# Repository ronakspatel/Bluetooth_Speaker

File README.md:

# Bluetooth Speaker Project  

Hello! My name is **Ronak Patel**, and this repository contains my work on building a **Bluetooth speaker with a metadata display**.  

At a high level, the flow from **phone → speaker** involves:  
1. Reception of the Bluetooth audio signal  
2. Conversion to analog audio  
3. Amplification and playback  

While commercial modules worked out of the box, I wanted to explore improvements and unique features:  
- A **portable speaker** with a **metadata display** (song title, artist, album)  
- An **audio visualizer** running on a TFT screen  
- My **first custom amplifier PCB**, designed in *KiCad*, to replace a noisy off-the-shelf board  

This project became an opportunity to learn the **full EE process**: embedded programming (ESP32), PCB design, and iterative prototyping.  

---

## High-Level Design  

### ESP32-WROOM-32 (Bluetooth Classic, A2DP sink)  
- Uses the [pschatzmann A2DP library](https://github.com/pschatzmann/ESP32-A2DP)  
- Supports **Bluetooth Classic**, which is required for A2DP audio  
- Provides metadata callback for song information  

### PCM5102A DAC  
- Converts I²S stream from ESP32 into high-quality analog audio  
- Chosen instead of ESP32’s internal 8-bit DAC (too low quality)  

### 1.8" TFT Display (128×160 px)  
- Upper half: **metadata** (title, artist, album)  
- Lower half: **audio visualizer** via FFT bins  
- Smooth GUI achieved by pushing the display as a **sprite**  

### Power System  
- **3S2P Li-ion battery pack** + **buck converter**  
- Amplifier powered directly from the battery via DC barrel jack  
- ESP32 power tapped via screw terminal  

---

## Amplifier Board (Custom PCB)  

### TPA3116D2 (Class D Audio Amp)  
- High power output, good fidelity  
- Efficient for **battery-powered** audio  

### TPS611781 (Boost Converter)  
- Steps up battery to ~19.6V  
- Stable voltage maximizes amplifier power output  

### NE5532 Op-Amp + RK09712200MY Potentiometer  
- Provides **stereo volume control**  
- Low output impedance prevents input impedance mismatch  

---

## Current Status  

- Speaker is **functional**, with enclosure designed (cutting pending)  
- Issues with the **RK09712200MY pot** (rated for 9V, running at 20V):  
  - Behaves like a balance control instead of volume  
  - Both output channels not stable under all loads  
- Audio visualizer: bass frequencies **dominate FFT output**, needs better equalization  

---

## Future Improvements  
- Integrate **all components** into one PCB  
- Refine **FFT visualization** for better frequency distribution  
- Replace problematic **potentiometer** with a properly rated alternative  
- Improve **enclosure fabrication** for a polished final product  

---

## Pictures

---

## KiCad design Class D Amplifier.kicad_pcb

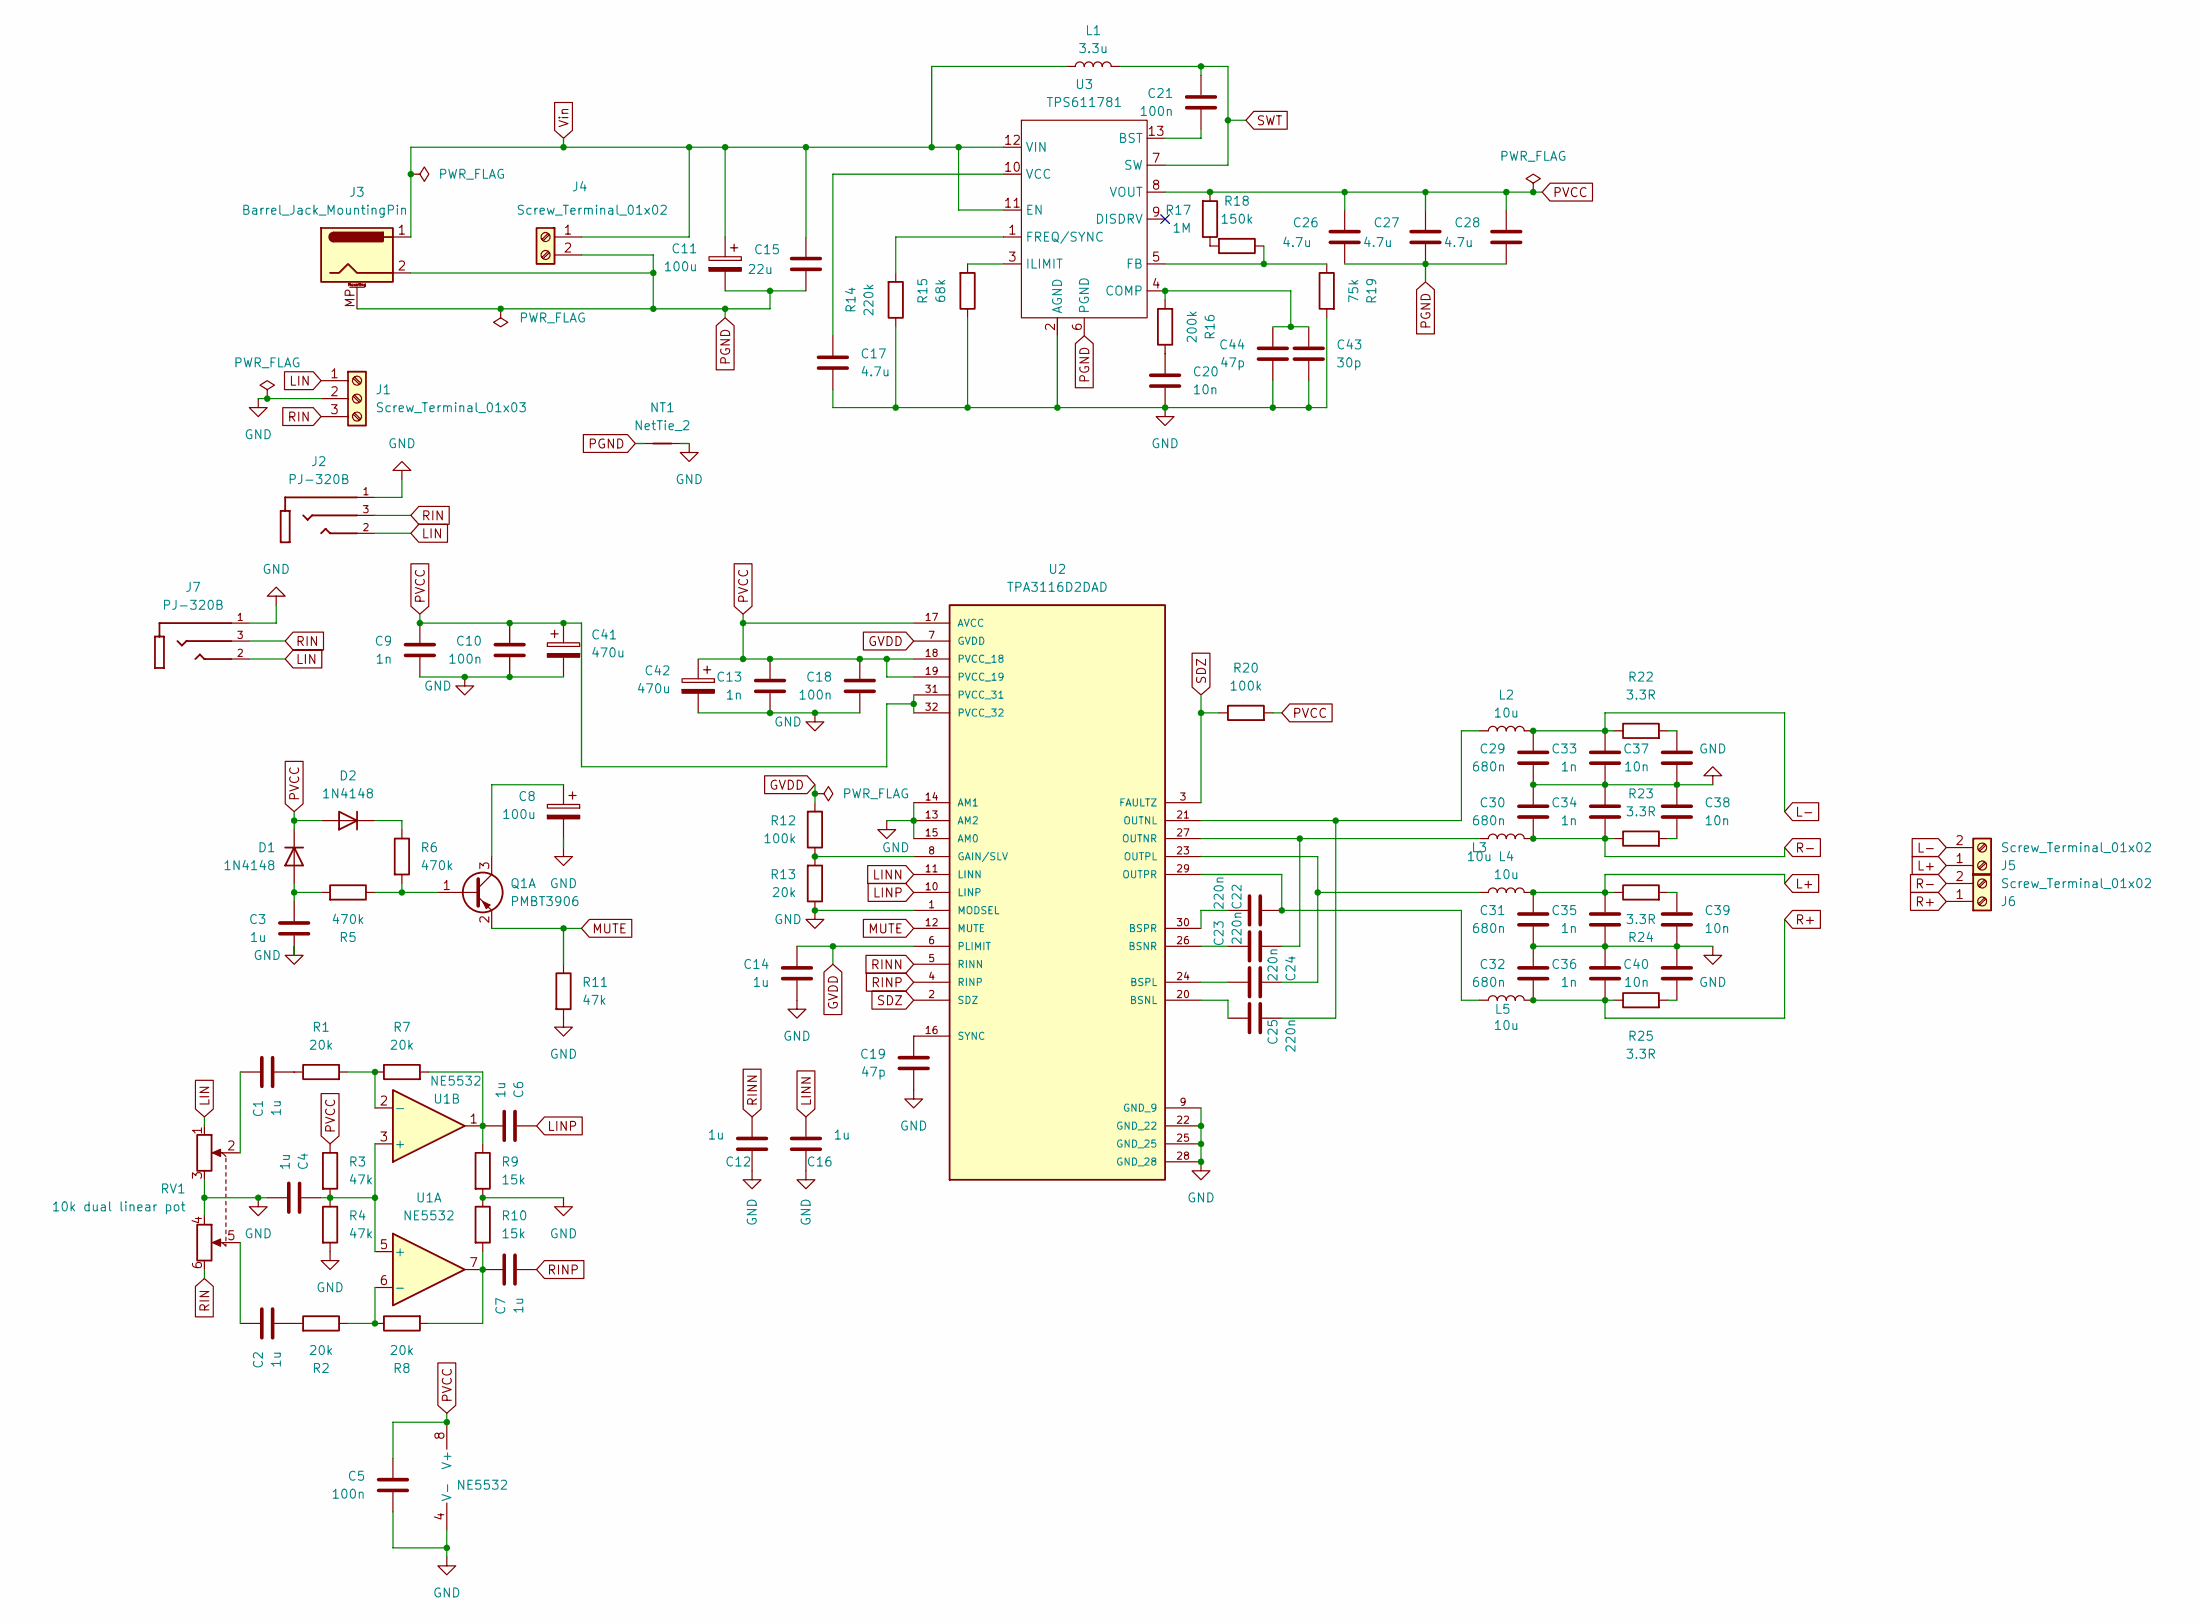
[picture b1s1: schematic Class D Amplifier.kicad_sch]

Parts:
C1, C2, C3, C4, C6, C7, C12, C14, C16: 1u; C_0805_2012Metric
C5, C10, C18: 100n; C_0805_2012Metric
C8, C11: 100u; CP_Radial_D6.3mm_P2.50mm
C9, C13, C33, C34, C35, C36: 1n; C_0805_2012Metric
C15: 22u; C_0805_2012Metric
C17, C26, C27, C28: 4.7u; C_0805_2012Metric
C19: 47p; C_0805_2012Metric
C20: 10n; C_0603_1608Metric
C21: 100n; C_0603_1608Metric
C22, C23, C24, C25: 220n; C_0805_2012Metric
C29, C30, C31, C32: 680n; C_Rect_L7.0mm_W3.5mm_P5.00mm
C37, C38, C39, C40: 10n; C_0805_2012Metric
C41, C42: 470u; CP_Radial_D10.0mm_P5.00mm
C43: 30p; C_0603_1608Metric
C44: 47p; C_0603_1608Metric
D1, D2: 1N4148; D_SOD-123
J1: Screw_Terminal_01x03; TerminalBlock_bornier-3_P5.08mm
J2, J7: PJ-320B; AUDIO_TH_PJ-3210-4A
J3: Barrel_Jack_MountingPin; BarrelJack_CUI_PJ-063AH_Horizontal
J4, J5, J6: Screw_Terminal_01x02; TerminalBlock_bornier-2_P5.08mm
L1: 3.3u; L_Sunlord_MWSA1003S
L2, L3, L4, L5: 10u; L_KOHERelec_MDA7030
NT1: NetTie_2; NetTie-2_SMD_Pad0.5mm
Q1: PMBT3906; SOT-23-3
R1, R2, R7, R8, R13: 20k; R_0805_2012Metric
R3, R4, R11: 47k; R_0805_2012Metric
R5, R6: 470k; R_0805_2012Metric
R9, R10: 15k; R_0805_2012Metric
R12, R20: 100k; R_0805_2012Metric
R14: 220k; R_0603_1608Metric
R15: 68k; R_0603_1608Metric
R16: 200k; R_0603_1608Metric
R17: 1M; R_0603_1608Metric
R18: 150k; R_0603_1608Metric
R19: 75k; R_0603_1608Metric
R22, R23, R24, R25: 3.3R; R_0805_2012Metric
RV1: 10k dual linear pot; Potentiometer_Alps_RK097_Dual_Horizontal
U1: NE5532; SOIC-8_3.9x4.9mm_P1.27mm
U2: TPA3116D2DAD; SOP65P810X115-32N; PARTREV G
U3: TPS611781; RNW0013A

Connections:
GVDD: C14.1, R12.2, U2.6 (PLIMIT), U2.7 (GVDD)
L+: C31.1, C35.1, J5.1, L4.1, R24.1
L-: C29.1, C33.1, J5.2, L2.2, R22.1
LIN: J1.1, J2.2, J7.2, RV1.1
LINN: C16.2, U2.11 (LINN)
MUTE: Q1.2 (E1), R11.1, U2.12 (MUTE)
unnamed: C1.1, RV1.2
unnamed: C1.2, R1.1
unnamed: C2.1, RV1.5
unnamed: C2.2, R2.2
unnamed: C7.1, R8.2, R10.2, U1.7
unnamed: C20.1, R16.1
unnamed: C37.1, R22.2
unnamed: C38.1, R23.2
unnamed: C39.1, R24.2
unnamed: C40.1, R25.2
unnamed: C3.1, D1.2 (A), R5.2
unnamed: D2.1 (K), R6.1
unnamed: Q1.1 (B1), R5.1, R6.2
unnamed: C8.1, Q1.3 (C1)
unnamed: R17.1, R18.2
unnamed: C4.1, R3.2, R4.1, U1.3 (+), U1.5 (+)
unnamed: R1.2, R7.1, U1.2 (-)
unnamed: R2.1, R8.1, U1.6 (-)
unnamed: C25.1, U2.20 (BSNL)
unnamed: C23.1, U2.26 (BSNR)
unnamed: C24.2, U2.24 (BSPL)
unnamed: C22.2, U2.30 (BSPR)
unnamed: R12.1, R13.2, U2.8 (GAIN/SLV)
unnamed: C25.2, L2.1, U2.21 (OUTNL)
unnamed: C23.2, L3.1, U2.27 (OUTNR)
unnamed: C24.1, L4.2, U2.23 (OUTPL)
unnamed: C22.1, L5.2, U2.29 (OUTPR)
unnamed: C19.1, U2.16 (SYNC)
unnamed: C21.2, U3.13 (BST)
unnamed: C43.1, C44.1, R16.2, U3.4 (COMP)
unnamed: R18.1, R19.1, U3.5 (FB)
unnamed: R14.2, U3.1 (FREQ/SYNC)
unnamed: R15.2, U3.3 (ILIMIT)
unnamed: C17.1, U3.10 (VCC)
PGND: C11.2, C15.2, C26.2, C27.2, C28.2, J3.2, J3.MP (MountPin), J4.2, NT1.1, U3.6 (PGND)
R+: C32.1, C36.2, J6.1, L5.1, R25.1
R-: C30.1, C34.2, J6.2, L3.2, R23.1
RIN: J1.3, J2.3, J7.3, RV1.6
RINN: C12.2, U2.5 (RINN)
RINP: C7.2, U2.4 (RINP)
SDZ: R20.1, U2.2 (SDZ), U2.3 (FAULTZ)
SWT: C21.1, L1.2, U3.7 (SW)
Vin: C11.1, C15.1, J3.1, J4.1, L1.1, U3.11 (EN), U3.12 (VIN)

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
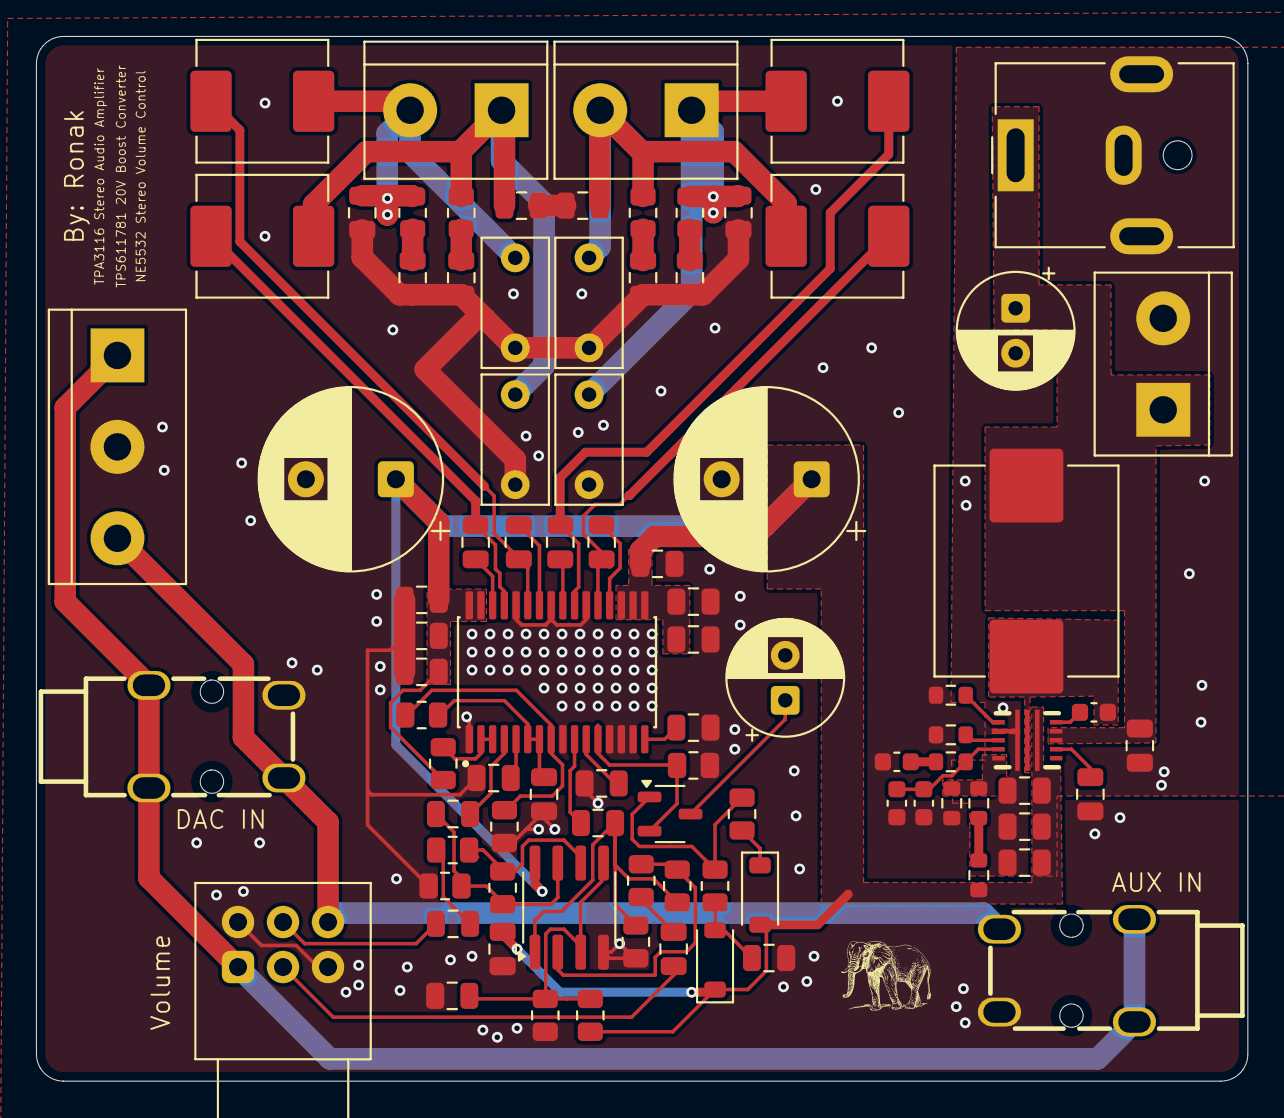
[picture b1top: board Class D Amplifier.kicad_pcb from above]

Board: 2 copper layers, 67.3 x 58.0 mm, 90 parts (0 on the bottom side), 53 nets.

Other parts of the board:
C6#2: 1u; C_0805_2012Metric
C8#2: 10n; C_0805_2012Metric

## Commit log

2025-09-01 Create Audio Amp PCB
2025-09-01 Create y
